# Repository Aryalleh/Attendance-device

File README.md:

**English** | [فارسی](README.fa.md)

# RFID attendance & access control (Wemos D1 mini or ESP32 + RC522)

A card reader that identifies people by RFID card and shows the result with LEDs
and a buzzer: green and a short beep for allowed cards, red and an alarm for unknown
or blocked cards. It logs every entry and exit with date and time. An optional relay
output can drive an electric lock.

📖 **Assembly guide:** [English](docs/assembly-en.md) · [فارسی](docs/assembly-fa.md)
📄 **Project proposal (Persian):** [docs/proposal-fa.md](docs/proposal-fa.md)

```
            ┌───────────── server mode ──────────────┐
 card ─► RC522 ─► Wemos D1 mini ──Wi-Fi──► server (Raspberry Pi, Flask + SQLite)
                   │  LEDs, buzzer              web panel: cards, devices, log,
                   │  (optional relay → lock)   attendance, who's inside, live screen
                   └─ standalone mode: cards + log + panel on the Wemos itself
```

| | **Server mode** | **Standalone mode** |
|---|---|---|
| Who decides | the server | the Wemos |
| Card list / log | SQLite on the server | flash on the Wemos (≤200 cards, ~2000 log lines) |
| Admin panel | server: `http://<pi>:8080` | device: `http://<device-name>.local` or its IP |
| Multiple devices | yes, shared card list | each device is independent |
| Server down? | keeps working from a cached card list; events are uploaded later | n/a |
| Needs a router | yes | no: the device can create its own Wi-Fi |

You switch modes in the device's own panel (Settings → Mode). No display is needed on the device.

## Repository layout

| Folder | Contents |
|---|---|
| `firmware/` | Device firmware for the Wemos D1 mini or an ESP32 DevKit (C++, PlatformIO) |
| `server/` | Server and web panel (Python, Flask, SQLite) |
| `hardware/` | Carrier PCB (KiCad 10): schematic, 2-layer layout, gerbers, renders |
| `docs/` | Assembly guide (EN/FA) and project proposal |
| `cloudflare/` | Optional: the same server on Cloudflare Workers ([its README](cloudflare/README.md)) |
| `android/` | Optional: Android app that turns an NFC phone into an online-only door device with a kiosk screen ([its README](android/README.md)) |

---

## 1. Hardware

The device is powered **from USB** (5 V into the Wemos's micro-USB port). The Wemos's
regulator makes 3.3 V for the RC522. Full step-by-step instructions are in the
[assembly guide](docs/assembly-en.md).

| Part | Notes |
|---|---|
| Wemos D1 mini (ESP8266) **or** ESP32 DevKit (ESP-WROOM-32, 30/38-pin) | see [ESP32 wiring](#esp32-devkit-wiring) for the ESP32 |
| RC522 RFID module + 13.56 MHz cards/tags | **3.3 V only** |
| Green LED + red LED + 2 × 220 Ω resistors | or an LED module |
| Buzzer | a low-level-trigger buzzer module, or a 5 V active buzzer with the 2-transistor driver from the assembly guide |
| USB cable (data-capable) + 5 V USB adapter | ≥ 500 mA |
| *Optional:* relay module + electric lock | needs its own lock supply; see the [relay note](#optional-relay-and-lock) |

### Carrier PCB (optional)

The KiCad design is in [`hardware/`](hardware/README.md): a 2-layer, 85 × 40 mm, all through-hole
board. The D1 mini and the RC522 plug into sockets, and the board carries the LEDs, the buzzer driver
(option B in the assembly guide) and a 3-pin header for an optional relay module. Gerbers:
[`hardware/fab/rfid-door-controller-gerbers.zip`](hardware/fab/rfid-door-controller-gerbers.zip).

| 3D, top | 3D |
|---|---|
|  |  |

Routing (red = top copper, blue = bottom copper, both with a ground pour):

| Top copper | Bottom copper (seen from below) |
|---|---|
|  |  |

Schematic ([PDF](hardware/rfid-door-controller-schematic.pdf)):

### Wiring

| RC522 | Wemos | | Module | Wemos |
|---|---|---|---|---|
| SDA (SS) | D8 | | Green LED | D1 |
| SCK | D5 | | Red LED | D2 |
| MOSI | D7 | | Buzzer | D3 |
| MISO | D6 | | *(optional)* Relay IN | D4 |
| RST | D0 | | | |
| 3.3V | 3V3 | | | |
| GND | G | | | |
| IRQ | — | | | |

SCK/MISO/MOSI (D5/D6/D7) are the ESP8266's hardware SPI pins and can't be moved.
D3/D4 must be HIGH and D8 LOW at boot. That is why the buzzer on D3 must be **silent when
its input is HIGH**: use a low-level-trigger module or the transistor driver, and set
`BUZZER_ACTIVE_LOW true` in `firmware/src/config.h`. D4 is also the Wemos's on-board
LED, so that LED lights while access is granted.

Pins and active-high/low polarity are set in `firmware/src/config.h`.

### ESP32 DevKit wiring

The same firmware also runs on an ESP32 DevKit (ESP-WROOM-32). The RC522 uses the ESP32's
default SPI pins:

| RC522 | ESP32 | | Module | ESP32 |
|---|---|---|---|---|
| SDA (SS) | G5 | | Green LED | G25 |
| SCK | G18 | | Red LED | G26 |
| MOSI | G23 | | Buzzer | G27 |
| MISO | G19 | | *(optional)* Relay IN | G32 |
| RST | G0 | | | |
| 3.3V | 3V3 | | | |
| GND | GND | | | |
| IRQ | — | | | |

The ESP32 has no boot-pin limits on G25/G26/G27/G32, so any buzzer works there. Set
`BUZZER_ACTIVE_LOW` to match your buzzer. G0 is also the board's **BOOT** button, so
holding BOOT resets the reader. To move RST, change `PIN_RC522_RST` in `config.h`
(G4 or G22 are good choices). The carrier PCB in `hardware/` is for the D1 mini only.
Power the DevKit from its USB port; its 3V3 pin feeds the RC522.

### Signals

| What you see/hear | Meaning |
|---|---|
| short beep + green | access granted (entry/exit logged) |
| 3 × red + beep | blocked / expired card |
| 1 long red + beep | unknown card |
| green/red alternating | waiting for a card to enroll (standalone) |
| short red flash every 3 s | server mode: server unreachable (using offline cache) |
| slow red blink | setup Wi-Fi hotspot is open (not connected to the router) |
| 3 × red, no beep at boot | RC522 not detected: check wiring |

---

## 2. Firmware

Install [PlatformIO](https://platformio.org/) (VS Code extension or `pip install platformio`), then:

```bash
cd firmware
pio run -t upload                 # Wemos D1 mini: build + flash
pio run -e esp32dev -t upload     # ESP32 DevKit: build + flash
pio device monitor                # serial log, 115200 baud
```

On some ESP32 boards you have to hold **BOOT** while the upload starts.

Don't run `pio run -t uploadfs`: it erases the saved settings and cards.

### First start

1. On first boot the device opens a Wi-Fi hotspot **`RFID-Setup-xxxxxx`**, password **`rfid12345`**.
2. Connect to it and open **http://192.168.4.1**. Log in as **admin / admin**.
3. In **Settings**, choose a mode, fill in the Wi-Fi and server settings, **change the admin password**, then press *Save & reboot*.

If the router is unreachable at boot, the setup hotspot opens again. The device keeps
working meanwhile, and the hotspot closes once the router is reachable.

### Standalone (small teams)

- **Add cards:** on the Cards tab, type a name, press **Scan to add**, then hold the card on the reader.
  Or scan an unknown card first: the Status tab then offers **Add this card**.
- **Block, allow or delete** cards from the same list.
- **Log tab:** shows the latest 100 events. **Download CSV** exports the whole log in your browser's timezone.
- **No router:** tick *"No router — this device creates its own Wi-Fi"*. The device then runs
  hotspot `<device name>` with your password at http://192.168.4.1. The clock is set from your
  phone or PC whenever you open the panel. With a router, it uses NTP instead.
- **Direction:** `toggle` makes scans alternate in → out → in. Use `in` or `out` for a reader that only handles one side.

### Server mode

1. In the server panel, go to **Doors → Add**. Copy the **device key** shown (it is shown only once).
2. In the device panel, set Mode = Server, enter the **Server URL** (e.g. `http://192.168.1.10:8080`) and the **Device key**.
3. Scan a new card. It appears on the server dashboard under **Unregistered cards**, where you click **Register**.

The device sends a heartbeat every 5 s. Through it, the device downloads the card list whenever it
changes, picks up "Open" commands from the panel, takes its clock from the server, and uploads
events it decided while offline (marked *offline* in the log). To refuse all cards while the
server is down, untick *"use the cached card list"*.

---

## 3. Server (Raspberry Pi or any Linux box)

```bash
sudo mkdir -p /opt/accessctl && sudo chown $USER /opt/accessctl
cp -r server /opt/accessctl/
python3 -m venv /opt/accessctl/venv
/opt/accessctl/venv/bin/pip install -r /opt/accessctl/server/requirements.txt

# try it
cd /opt/accessctl/server && ACCESSCTL_DATA=/opt/accessctl/data ../venv/bin/python app.py
```

The first start prints the generated password for **admin**, the server owner. Open `http://<pi-ip>:8080`.

To run it as a service, next to whatever else the Pi is doing, edit `User=` in
`server/accessctl.service`, then:

```bash
sudo cp server/accessctl.service /etc/systemd/system/
sudo systemctl daemon-reload && sudo systemctl enable --now accessctl
journalctl -u accessctl -f
```

It's a single process (waitress, 8 threads) with one SQLite file in `ACCESSCTL_DATA`.
Back up `access.db` and `secret_key` from that folder.
To reset a password: `../venv/bin/python app.py set-password admin` (an unknown name creates a new server owner).

### Companies and users

One server can host several **companies** (or teams) that have nothing to do with each other.
Each company has its own panel users, cards, devices, logs and classes, and never sees another company's data.

- **Server owner** (`admin`, and any owner you add): logs in to **مدیریت سرور** (`/admin`). There you create a company
  together with its first login, add or remove its users, reset passwords, disable it (its users can't log in and its
  devices refuse every card) or delete it with all its data. **ورود به پنل** opens any company's panel.
- **Company users** see only their own panel. They create their own **devices** (each gets a key for the Wemos or the
  Android app), register cards, define classes and add more users for their company under Settings.
- The same card UID can be registered in two companies. Device keys are unique across the server, so a scan always
  belongs to the company that owns the device.

Upgrading from the single-company version is automatic: on first start the existing cards, doors and logs move into a
company called «سازمان پیش‌فرض», and the existing logins become server owners. Rename it on the admin page.

### Classes (attendance per class)

On the **کلاس‌ها** page a company creates classes, picks the **members** (from its cards) and links the class to a
**device at set times**:

- **weekly**: one or more weekdays and a time range, optionally between two dates (without a start date it starts on
  the day you add it), or
- **once**: an extra session on a single date.

During a session, members scan their card on that device when they **enter** and again when they **leave**
(the device alternates in/out per session; a device set to entry-only or exit-only records that direction).
Cards of people who are not members are **refused** and logged as «عضو کلاس نیست». Scans are accepted from 15 minutes
before the start until 30 minutes after the end, so early arrivals and late exits are recorded, but only time inside
the class hours counts. An entry with no exit counts until the end of the class and is flagged «خروج ثبت نشد».
Outside class times the device works as a normal door.

Each class page shows, for a date range (last 30 days by default):
- every **session** with how many members came, and per session each member's **entry time, exit time and time in
  class** (absent members are marked «غایب»), plus refused cards;
- a **summary per member**: sessions attended, total time in class and attendance percentage, with CSV export.

The dashboard lists classes that are running now and how many members are inside.

### Panel

Both panels (server and device) are in **Persian, right-to-left**. Dates are shown in the
**Shamsi (Jalali) calendar** with Persian digits. Date fields take Shamsi dates such as
`1405/08/11` (Persian digits work too). CSV exports include Shamsi and Gregorian dates and
start with a UTF-8 BOM, so Excel displays Persian names correctly. The server bundles the
Vazirmatn font (`static/fonts`, SIL OFL), so it doesn't need internet. The device panel uses
the system font (Tahoma/Segoe UI).

- **Live screen** (landing page, `/`): a full-screen display for a tablet or monitor by the door. It shows the
  person's name with a green ✓ «خوش آمدید / خدانگهدار», or a red ✗ «دسترسی رد شد» with the reason (unknown card,
  blocked or expired). Each scan plays a sound through the browser (Web Audio, no audio files needed). It also shows
  a clock in Shamsi date and the last 10 scans. Tap the screen once so the browser allows sound, and use the ⛶ button
  for full screen. **Doors → نمایشگر** gives each device a private link that works **without logging in**.
  Anyone with the link can see that device's scans, and **New key** revokes it.
- **Dashboard** (`/dashboard`): who is inside, today's counts, device online/offline status, unregistered cards, recent activity.
- **Cards**: add, edit, block or allow; optional **valid-until** date and a note; per-card history.
- **Devices**: direction (entry, exit or toggle), enable/disable, new key, live-screen link.
- **Classes**: members, weekly or one-off schedules on a device, per-session and per-member attendance reports.
- **Log**: filter by name, UID, result, device, class and date; CSV export.
- **Daily attendance**: first in, last out and time on site per person per day.
- **Parent link** (on each card's page): a private page, no login, where parents see whether their child is at school now, when they arrived and left today, and the last 14 days. **New link** revokes the old one; **Disable** turns it off. Anyone with the link can see that one child's times, so give it only to the family.
- **Settings**: the company's panel users, purging the company's old events.
- **Server admin** (owners only): companies, their users, integrations.

### Hooking it into other things on the server

- `ACCESSCTL_WEBHOOK_URL=http://…`: every event of every company is POSTed as JSON, e.g.
  `{"time": "...", "org": "Acme", "org_id": 2, "door": "Main", "name": "Sara", "uid": "04:A3:1B:2C", "result": "granted", "direction": "in", "class_id": null, "offline": false}`.
  Works with Node-RED, Home Assistant, a Telegram bot, etc.
- `ACCESSCTL_API_TOKEN=…` enables `GET /api/v1/presence` and `GET /api/v1/events?since=<id>`
  (header `Authorization: Bearer <token>`). The token is the server owner's: it reads all companies; add `&org=<id>`
  to limit it to one.

### Device ↔ server protocol

All requests carry the header `X-Device-Key: <key>`.

| Call | Body | Reply |
|---|---|---|
| `POST /api/v1/scan` | `{"uid":"04:A3:1B:2C"}` | `{"granted":true,"result":"granted","name":"Sara","direction":"in","open_ms":3000}` |
| `POST /api/v1/sync` | `{"fw":"1.0.0","cards_version":"…","events":[{ts,uid,result,direction}…]}` | `{"time":…,"cards_version":"…","open":false,"open_ms":3000}` |
| `GET /api/v1/cards` | — | TSV lines `uid⇥1⇥inside⇥name` (valid cards only) |
| `GET /api/v1/kiosk` | — | `{"name":"Front door","url":"/kiosk/<token>"}` — this door's live-screen link (used by the Android app) |

`result` is one of `granted | unknown | disabled | expired | denied | not_member` (denied = device or company disabled;
not_member = scanned during a class session by someone who isn't a member).

---

## Optional: relay and lock

The firmware also drives a relay on **D4** for `open_ms` milliseconds (default 3 s) on every
granted scan, and on **Open** from the panel. To use it, connect an active-LOW relay module
(`RELAY_ACTIVE_LOW true`) to D4 and give the lock **its own power supply**. Don't power a
lock from the Wemos's USB 5 V. Put a flyback diode across the lock coil, and keep a
mechanical or exit-button release on the inside of the door.

---

## Security notes

- Basic 13.56 MHz cards (MIFARE Classic, cheap tags) **can be cloned**. Only the UID is checked,
  so this suits attendance in offices, labs and classrooms, not high-security doors.
- The device panel uses HTTP Basic auth, and device ↔ Flask server traffic is plain HTTP. Keep both
  on a trusted LAN or Wi-Fi, and don't port-forward them to the internet.
- Change `admin/admin` and the hotspot password on first setup.

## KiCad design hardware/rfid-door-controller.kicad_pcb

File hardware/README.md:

# Carrier board (KiCad 10)

A 2-layer, 85 × 40 mm, all through-hole carrier for the RFID attendance device:
the Wemos D1 mini plugs into two 1×8 female headers, the RC522 into a 1×8
socket on the left edge, and the board adds the two status LEDs, the buzzer
driver and a header for an optional relay module.

| Ref | Part | Notes |
|---|---|---|
| A1 | Wemos D1 mini | Two 1×8 female headers. Antenna at the top edge, USB at the bottom edge |
| J1 | 1×8 female socket, RC522 | SDA SCK MOSI MISO IRQ GND RST 3.3V, pin 1 at the bottom |
| C1 | 100 nF | RC522 3.3 V decoupling |
| C2 | 47 µF 10 V | 5 V bulk for the buzzer and relay module |
| R1, D1 | 220 Ω, green 5 mm LED | D1 pin, active HIGH |
| R2, D2 | 220 Ω, red 5 mm LED | D2 pin, active HIGH |
| R3, Q1, R4, Q2 | 47 k, BC547, 10 k, BC337 | Inverting buzzer driver: silent at boot |
| BZ1 | 5 V active buzzer, 7.6 mm pitch | + to +5V |
| J2 | 1×3 pin header, optional | 1 +5V, 2 GND, 3 IN (D4) for an active-LOW relay module |

**Power** comes only from the D1 mini's micro-USB socket (5 V, ≥ 500 mA). The D1
mini's own regulator feeds the RC522 with 3.3 V. Give a door lock its own supply;
never run it from the USB 5 V.

**Firmware** (`firmware/src/config.h`) for this board:

```c
#define LED_ACTIVE_LOW     false
#define BUZZER_ACTIVE_LOW  true    // inverting driver: D3 LOW = beep, D3 HIGH at boot = silent
#define RELAY_ACTIVE_LOW   true    // active-LOW relay module on J2
```

## Files

| File | What it is |
|---|---|
| `generate_schematic.py` | Writes `rfid-door-controller.kicad_sch` and proves it against the netlist spec in the script |
| `place_board.py` | Creates and places `rfid-door-controller.kicad_pcb` from a coordinate table |
| `route_board.py` | Routes every net, adds GND stitching and pours, runs DRC |
| `schlib.py`, `pcblib.py`, `routelib.py` | The builder libraries the three scripts use |
| `rfid-door-controller-schematic.pdf` | The schematic, printed |
| `fab/` | Gerbers + drill (`fab/rfid-door-controller-gerbers.zip`) and `bom.csv` |
| `render/` | 3D renders, top and bottom |

The `.kicad_sch` and `.kicad_pcb` are generated: change the scripts, not the files,
or your edits are lost on the next run. (The scripts refuse to overwrite a file
that was edited in KiCad since they wrote it, and back it up first.)

## Regenerating

Needs KiCad 10: `kicad-cli` on the PATH for the schematic and KiCad's own Python
(`pcbnew`) for the board.

```bash
python3 generate_schematic.py            # schematic + netlist/ERC check
python3 generate_schematic.py --force    # after porting hand edits into the script
"$KPY" place_board.py --force            # resets every footprint to the table
"$KPY" route_board.py                    # tracks, vias, pours, DRC
```

`$KPY` is KiCad's Python: `/usr/bin/python3` on a distro KiCad, or
`"C:\Program Files\KiCad\10.0\bin\python.exe"` on Windows.

Fab outputs:

```bash
kicad-cli sch export pdf -o rfid-door-controller-schematic.pdf rfid-door-controller.kicad_sch
kicad-cli pcb export gerbers -o fab/gerbers/ rfid-door-controller.kicad_pcb
kicad-cli pcb export drill   -o fab/gerbers/ rfid-door-controller.kicad_pcb
```

## Checks

- Schematic: KiCad's netlist matches the spec in `generate_schematic.py` exactly;
  ERC has 0 errors.
- Board: DRC has 0 errors, 0 unconnected and 0 schematic-parity items. Any
  `lib_footprint_issues` mean that KiCad cannot find its stock footprint libraries
  (for example, a portable install with no library tables). They are not board faults.
- Both GND pours are each one piece, tied together by 17 stitching vias.

## Assembly notes

- Solder the low parts first: resistors, C1, the transistors (flat face as on the
  silkscreen), then the LEDs (long leg toward the resistor), C2 (the + mark),
  the buzzer (+ to the right), the headers, and the sockets last.
- Plug the D1 mini in with its USB socket toward the bottom edge. The antenna end
  sits over the copper-free area at the top edge.
- The RC522 plugs into J1 component side out, or connects through a cable no
  longer than 15 cm.

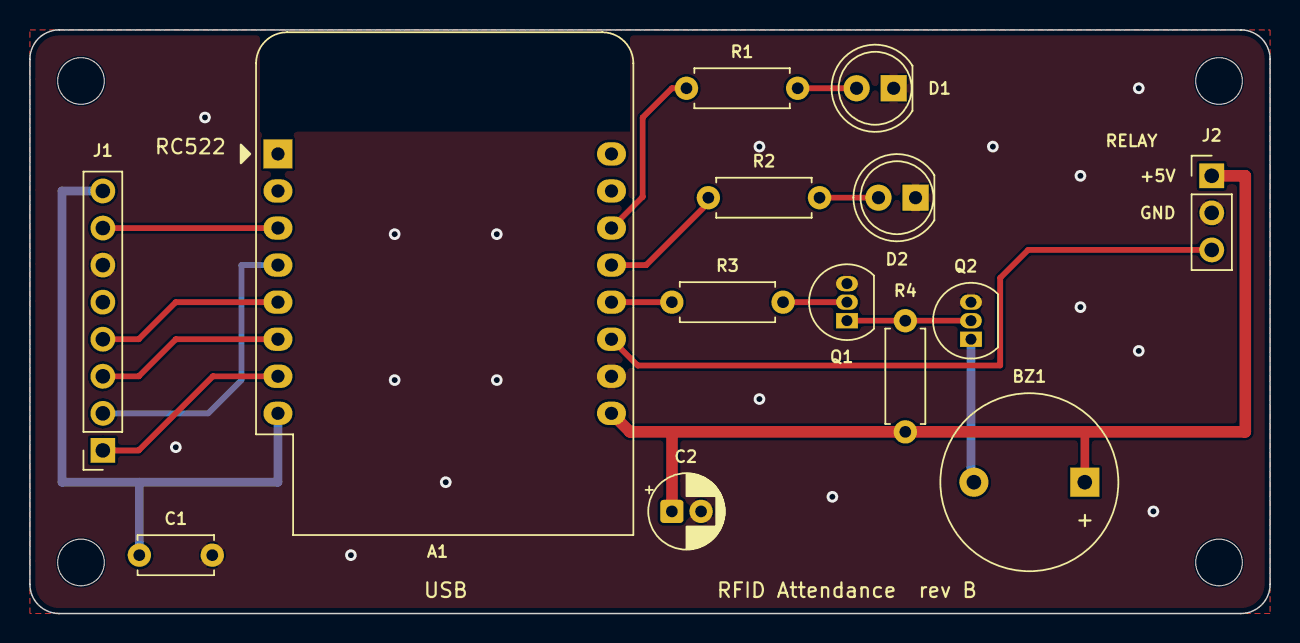
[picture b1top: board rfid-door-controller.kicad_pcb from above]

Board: 2 copper layers, 85.0 x 40.0 mm, 18 parts (0 on the bottom side), 17 nets.

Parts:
A1: WeMos D1 mini; WEMOS_D1_mini_light
BZ1: 5V active; Buzzer_12x9.5RM7.6
C1: 100nF; C_Disc_D5.0mm_W2.5mm_P5.00mm
C2: 47uF 10V; CP_Radial_D5.0mm_P2.00mm
D1: GREEN; LED_D5.0mm
D2: RED; LED_D5.0mm
H1, H2, H3, H4: MountingHole_3.2mm
J1: RC522; PinSocket_1x08_P2.54mm_Vertical
J2: RELAY (opt.); PinHeader_1x03_P2.54mm_Vertical
Q1: BC547; TO-92_Inline
Q2: BC337; TO-92_Inline
R1, R2: 220; R_Axial_DIN0207_L6.3mm_D2.5mm_P7.62mm_Horizontal
R3: 47k; R_Axial_DIN0207_L6.3mm_D2.5mm_P7.62mm_Horizontal
R4: 10k; R_Axial_DIN0207_L6.3mm_D2.5mm_P7.62mm_Horizontal

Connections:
+3V3: A1.8, C1.1, J1.8
+5V: A1.9, BZ1.1, C2.1, J2.1, R4.1
/BUZZER: A1.12, R3.1
/GREEN_LED: A1.14, R1.1
/RED_LED: A1.13, R2.1
/RELAY: A1.11, J2.3
/RFID_RST: A1.3, J1.7
/RFID_SS: A1.7, J1.1
/SPI_MISO: A1.5, J1.4
/SPI_MOSI: A1.6, J1.3
/SPI_SCK: A1.4, J1.2
GND: A1.10, C1.2, C2.2, D1.1, D2.1, J1.6, J2.2, Q1.3, Q2.3
unnamed: BZ1.2, Q2.1
unnamed: D1.2, R1.2
unnamed: D2.2, R2.2
unnamed: Q1.2, R3.2
unnamed: Q1.1, Q2.2, R4.2

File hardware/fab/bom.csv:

"Refs","Value","Footprint","Qty"
"A1","WeMos D1 mini","RF_Module:WEMOS_D1_mini_light","1"
"BZ1","5V active","Buzzer_Beeper:Buzzer_12x9.5RM7.6","1"
"C1","100nF","Capacitor_THT:C_Disc_D5.0mm_W2.5mm_P5.00mm","1"
"C2","47uF 10V","Capacitor_THT:CP_Radial_D5.0mm_P2.00mm","1"
"D1","GREEN","LED_THT:LED_D5.0mm","1"
"D2","RED","LED_THT:LED_D5.0mm","1"
"J1","RC522","Connector_PinSocket_2.54mm:PinSocket_1x08_P2.54mm_Vertical","1"
"J2","RELAY (opt.)","Connector_PinHeader_2.54mm:PinHeader_1x03_P2.54mm_Vertical","1"
"Q1","BC547","Package_TO_SOT_THT:TO-92_Inline","1"
"Q2","BC337","Package_TO_SOT_THT:TO-92_Inline","1"
"R1,R2","220","Resistor_THT:R_Axial_DIN0207_L6.3mm_D2.5mm_P7.62mm_Horizontal","2"
"R3","47k","Resistor_THT:R_Axial_DIN0207_L6.3mm_D2.5mm_P7.62mm_Horizontal","1"
"R4","10k","Resistor_THT:R_Axial_DIN0207_L6.3mm_D2.5mm_P7.62mm_Horizontal","1"

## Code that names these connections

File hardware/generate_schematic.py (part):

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    RC522 SDA/SS D8, SCK D5, MOSI D7, MISO D6, RST D0
    green LED D1, red LED D2, buzzer D3, optional relay module D4

D3 (GPIO0) is a boot strap that sits HIGH through reset, so the buzzer is
driven through an inverting two-transistor stage (assembly guide, option B):
it sounds when D3 goes LOW and stays silent while the board boots.
Firmware: BUZZER_ACTIVE_LOW true, RELAY_ACTIVE_LOW true (active-LOW relay module).
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        s.gnd(g[0], g[1] + 5.08)
        s.wire((g[0], g[1] + 2.54), (g[0] - 5.08, g[1] + 2.54))
        s.power("PWR_FLAG", g[0] - 5.08, g[1] + 2.54, rot=90)
        for pin, net in ((3, "RFID_RST"), (14, "GREEN_LED"), (13, "RED_LED"), (12, "BUZZER"),
                         (11, "RELAY"), (4, "SPI_SCK"), (5, "SPI_MISO"), (6, "SPI_MOSI"),
                         (7, "RFID_SS")):
            s.stub("A1", pin, 5.08, label=net)
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    with s.block("RC522 RFID READER"):
        x, y = 228.6, 60.96
        put(s, "J1", x, y, mirror="x")
        for pin, net in ((1, "RFID_SS"), (2, "SPI_SCK"), (3, "SPI_MOSI"), (4, "SPI_MISO"),
                         (7, "RFID_RST")):
            s.stub("J1", pin, 7.62, label=net)
        s.nc("J1", 5)
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        s.wire(s.pin("R3", 2), s.pin("Q1", "B"))
        p1 = s.pin("R3", 1)
        s.wire(p1, (p1[0] - 5.08, y))
        s.label("BUZZER", p1[0] - 5.08, y, angle=180)
        s.stub("Q1", "E", 2.54, power="GND")
        c = s.pin("Q1", "C")
        put(s, "Q2", c[0] + 22.86, c[1])
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        s.stub("BZ1", 1, 2.54, power="+5V")
        s.note("D3 HIGH (boot, idle): Q1 on, Q2 off, silent.\n"
               "D3 LOW: buzzer on. Firmware BUZZER_ACTIVE_LOW true.\n"
               "BZ1: 5 V ACTIVE buzzer (beeps on DC), + pin to +5V.",
               x - 22.86, y + 12.7, 1.0)


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        s.wire(e, (e[0], e[1] - 5.08))
        s.power("+5V", e[0], e[1] - 5.08)
        s.stub("J2", 2, 2.54, power="GND")
        s.stub("J2", 3, 7.62, label="RELAY")
        s.note("1 VCC  2 GND  3 IN, for an active-LOW 5 V relay module\n"
               "(RELAY_ACTIVE_LOW true). D4 is HIGH at boot: relay off.\n"
               "Give the lock its OWN supply -- never the USB 5 V --\n"
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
